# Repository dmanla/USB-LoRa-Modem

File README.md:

# USB-LoRa-Modem: Long-Range P2P Terminal

## Overview
**USB-LoRa-Modem** is an open-hardware radio terminal designed to enable any USB-equipped device to communicate over long distances using LoRa modulation. It is optimized for **secure, off-grid text communication** and provides a robust link in environments where cellular or Wi-Fi infrastructure is unavailable.

The core of the device is the **EByte E22-900T30S**, providing high-power **1-Watt (30dBm)** transmission in the US-legal **915MHz** ISM band, with a focus on maximum range and hardware-level signal isolation.

---

## Key Security & Design Features
* **Active-Discharge Kill Switch**: A physical SPDT slide switch (**SW1**) that disconnects the buck converter and actively shorts the internal power rail to ground through a **10Ω** resistor (**R4**). This ensures the **1080µF** bulk capacitance is drained instantly, preventing any residual "heartbeat" transmissions after power-off.
* **EMI & Signal Integrity**: **22Ω** series resistors (**R3, R7**) are placed on the UART data lines (TX, RX). This dampens high-frequency harmonics and limits radiated EMI, ensuring the device remains quiet and the signal remains clean.
* **Hardware Flow Control**: The LoRa module's **AUX** pin is tied to the **CTS** line of the **CH343P**. This allows the host software to automatically manage data buffers, preventing packet loss during high-volume wireless transmissions.
* **High-Current Power Path**: Features a **TPS62A01** synchronous buck converter capable of delivering **1A peak current** to handle the significant power draw of 30dBm LoRa transmissions without voltage brownouts.

---

## Major Components
| Component | Part Number | Description |
| :--- | :--- | :--- |
| **LoRa Module** | **E22-900T30S** | 30dBm (1W) LoRa Transceiver (SX1262 based). |
| **USB-UART Bridge** | **WCH CH343P** | High-speed USB to serial converter with CTS support. |
| **Power Regulator** | **TPS62A01ADRL** | 1000mA Synchronous Buck Converter (5V to 3.3V). |
| **ESD Protection** | **USBLC6-2SC6** | Low-capacitance ESD protection for USB data lines. |

---

## Technical Specifications
* **Input Power**: USB VBUS (+5V, up to 700mA peak).
* **Frequency**: 902–928 MHz (Standard US ISM Band).
* **Range**: ~10km+ Line-of-Sight (Antenna dependent).
* **Logic Level**: 3.3V TTL.
* **EDA Software**: **KiCad 9.0.7**.

---

## Usage
1.  **Enable Device**: Flip **SW1** to the `ON` position.
2.  **Communication**: Open a serial terminal (e.g., `pyserial` or `minicom`) at **9600** baud (default).
3.  **Configuration**: To send **AT Commands**, the device must be in Configuration Mode (Requires M0/M1 pins to be set according to your hardware strapping).
4.  **Kill Session**: Flip **SW1** to the `OFF` position. The power rail is immediately grounded, and the radio is physically silenced.

## Front 3D Render

## Back 3D Render

## License

All PCB design files and hardware are released under the [Creative Commons Attribution Share Alike 4.0](https://choosealicense.com/licenses/cc-by-sa-4.0/) license.

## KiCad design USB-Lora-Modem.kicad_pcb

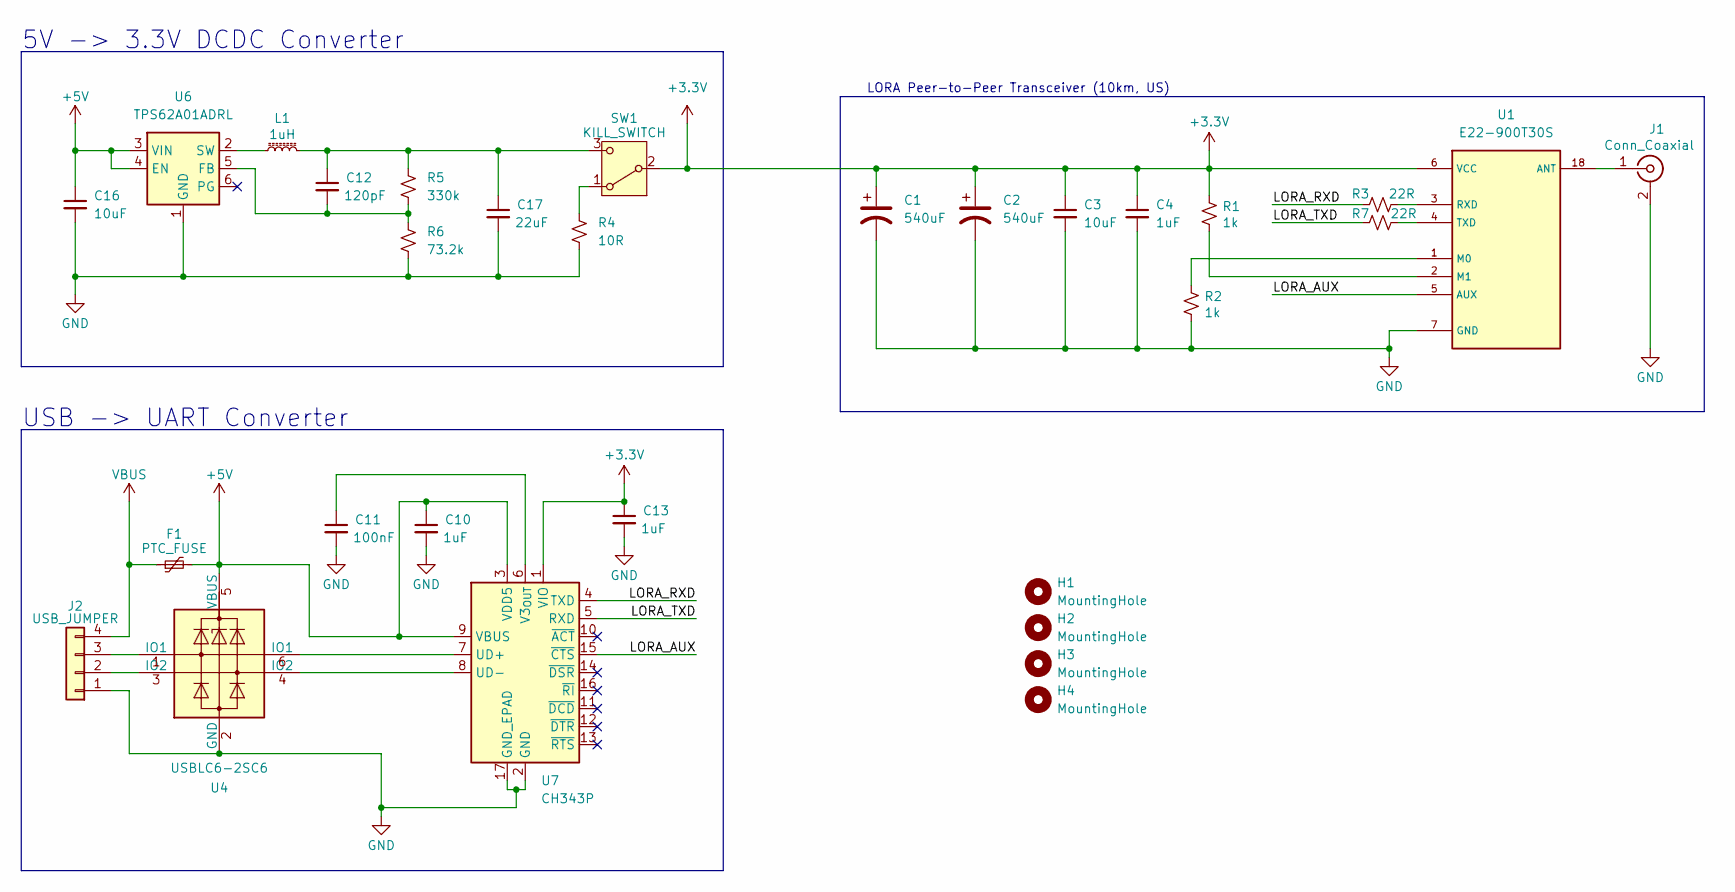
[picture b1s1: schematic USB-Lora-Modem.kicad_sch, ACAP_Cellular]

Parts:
C1, C2: 540uF; CP_EIA-7343-15_Kemet-W
C3: 10uF; C_0805_2012Metric_Pad1.18x1.45mm_HandSolder
C4, C10, C13: 1uF; C_0603_1608Metric_Pad1.08x0.95mm_HandSolder
C11: 100nF; C_0603_1608Metric_Pad1.08x0.95mm_HandSolder
C12: 120pF; C_0603_1608Metric_Pad1.08x0.95mm_HandSolder
C16: 10uF; C_0805_2012Metric
C17: 22uF; C_0805_2012Metric
F1: PTC_FUSE; Fuse_1206_3216Metric_Pad1.42x1.75mm_HandSolder
H1, H2, H3, H4: MountingHole; MountingHole_3.2mm_M3
J1: Conn_Coaxial; SMA_Amphenol_132289_EdgeMount
J2: USB_JUMPER; PinHeader_1x04_P2.54mm_Vertical
L1: 1uH; L_1210_3225Metric_Pad1.42x2.65mm_HandSolder
R1, R2: 1k; R_0603_1608Metric_Pad0.98x0.95mm_HandSolder
R3, R7: 22R; R_0603_1608Metric_Pad0.98x0.95mm_HandSolder
R4: 10R; R_1210_3225Metric_Pad1.30x2.65mm_HandSolder
R5: 330k; C_0603_1608Metric_Pad1.08x0.95mm_HandSolder
R6: 73.2k; C_0603_1608Metric_Pad1.08x0.95mm_HandSolder
SW1: KILL_SWITCH; SK-12F04-G050
U1: E22-900T30S; XCVR_E22-900T30S
U4: USBLC6-2SC6; SOT-23-6_Handsoldering
U6: TPS62A01ADRL; SOT-563
U7: CH343P; WCH_QFN-16-1EP_3x3mm_P0.5mm_EP1.8x1.8mm

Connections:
+3.3V: C1.1, C2.1, C3.1, C4.1, C13.1, R1.1, SW1.2 (B), U1.6 (VCC), U7.1 (VIO)
+5V: C10.1, C16.1, F1.2, U4.5 (VBUS), U6.3 (VIN), U6.4 (EN), U7.3 (VDD5), U7.9 (VBUS)
/LORA_AUX: U1.5 (AUX), U7.15 (~CTS)
/LORA_RXD: R3.1, U7.4 (TXD)
/LORA_TXD: R7.1, U7.5 (RXD)
GND: C1.2, C2.2, C3.2, C4.2, C10.2, C11.2, C13.2, C16.2, C17.2, J1.2 (Ext), J2.1, R2.2, R4.2, R6.2, U1.7 (GND), U1.9 (GND), U1.15 (GND), U1.16 (GND), U1.17 (GND), U4.2 (GND), U6.1 (GND), U7.2 (GND), U7.17 (GND_EPAD)
unnamed: J1.1 (In), U1.18 (ANT)
unnamed: J2.2, U4.3 (IO2)
unnamed: J2.3, U4.1 (IO1)
unnamed: R4.1, SW1.1 (A)
unnamed: C12.1, C17.1, L1.2, R5.1, SW1.3 (C)
unnamed: R2.1, U1.1 (M0)
unnamed: R1.2, U1.2 (M1)
unnamed: R3.2, U1.3 (RXD)
unnamed: R7.2, U1.4 (TXD)
unnamed: C12.2, R5.2, R6.1, U6.5 (FB)
unnamed: L1.1, U6.2 (SW)
unnamed: U4.6 (IO1), U7.7 (UD+)
unnamed: U4.4 (IO2), U7.8 (UD-)
unnamed: C11.1, U7.6 (V3_{OUT})
VBUS: F1.1, J2.4

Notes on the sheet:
LORA Peer-to-Peer Transceiver (10km, US)
5V -> 3.3V DCDC Converter
USB -> UART Converter

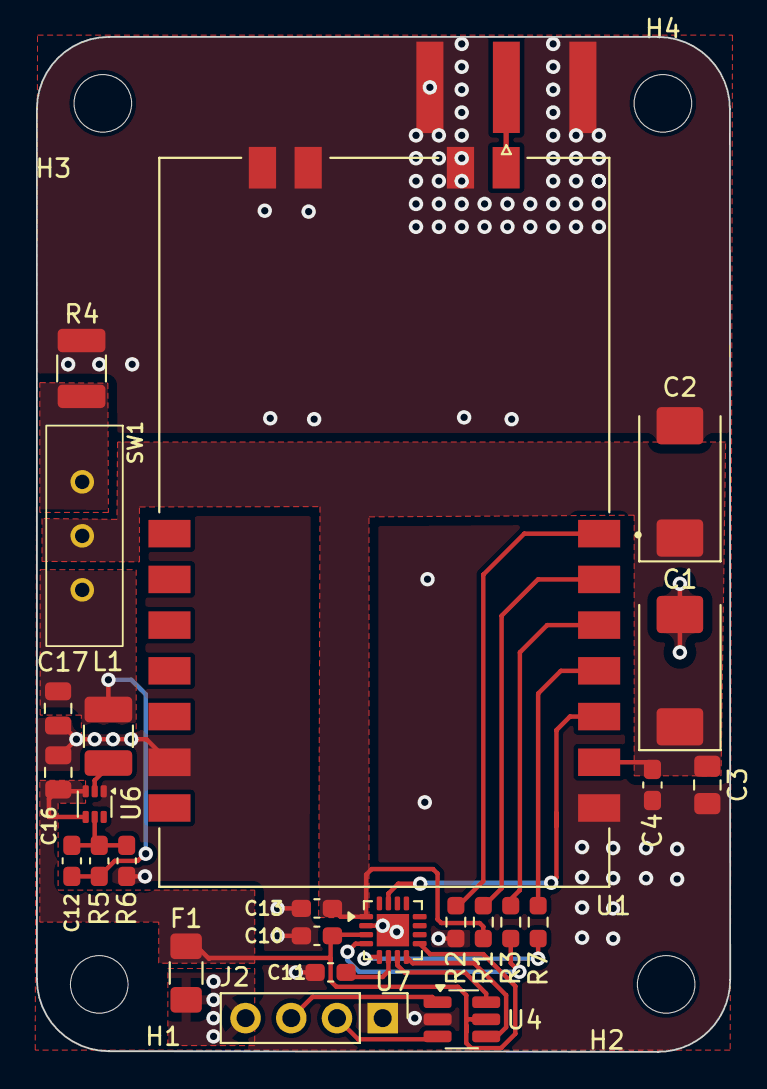
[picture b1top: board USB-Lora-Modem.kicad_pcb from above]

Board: 4 copper layers, 38.5 x 56.4 mm, 30 parts (0 on the bottom side), 21 nets.

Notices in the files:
USB-Lora-Modem.kicad_pcb:
Copyright: Tech Studio Design, 2021
